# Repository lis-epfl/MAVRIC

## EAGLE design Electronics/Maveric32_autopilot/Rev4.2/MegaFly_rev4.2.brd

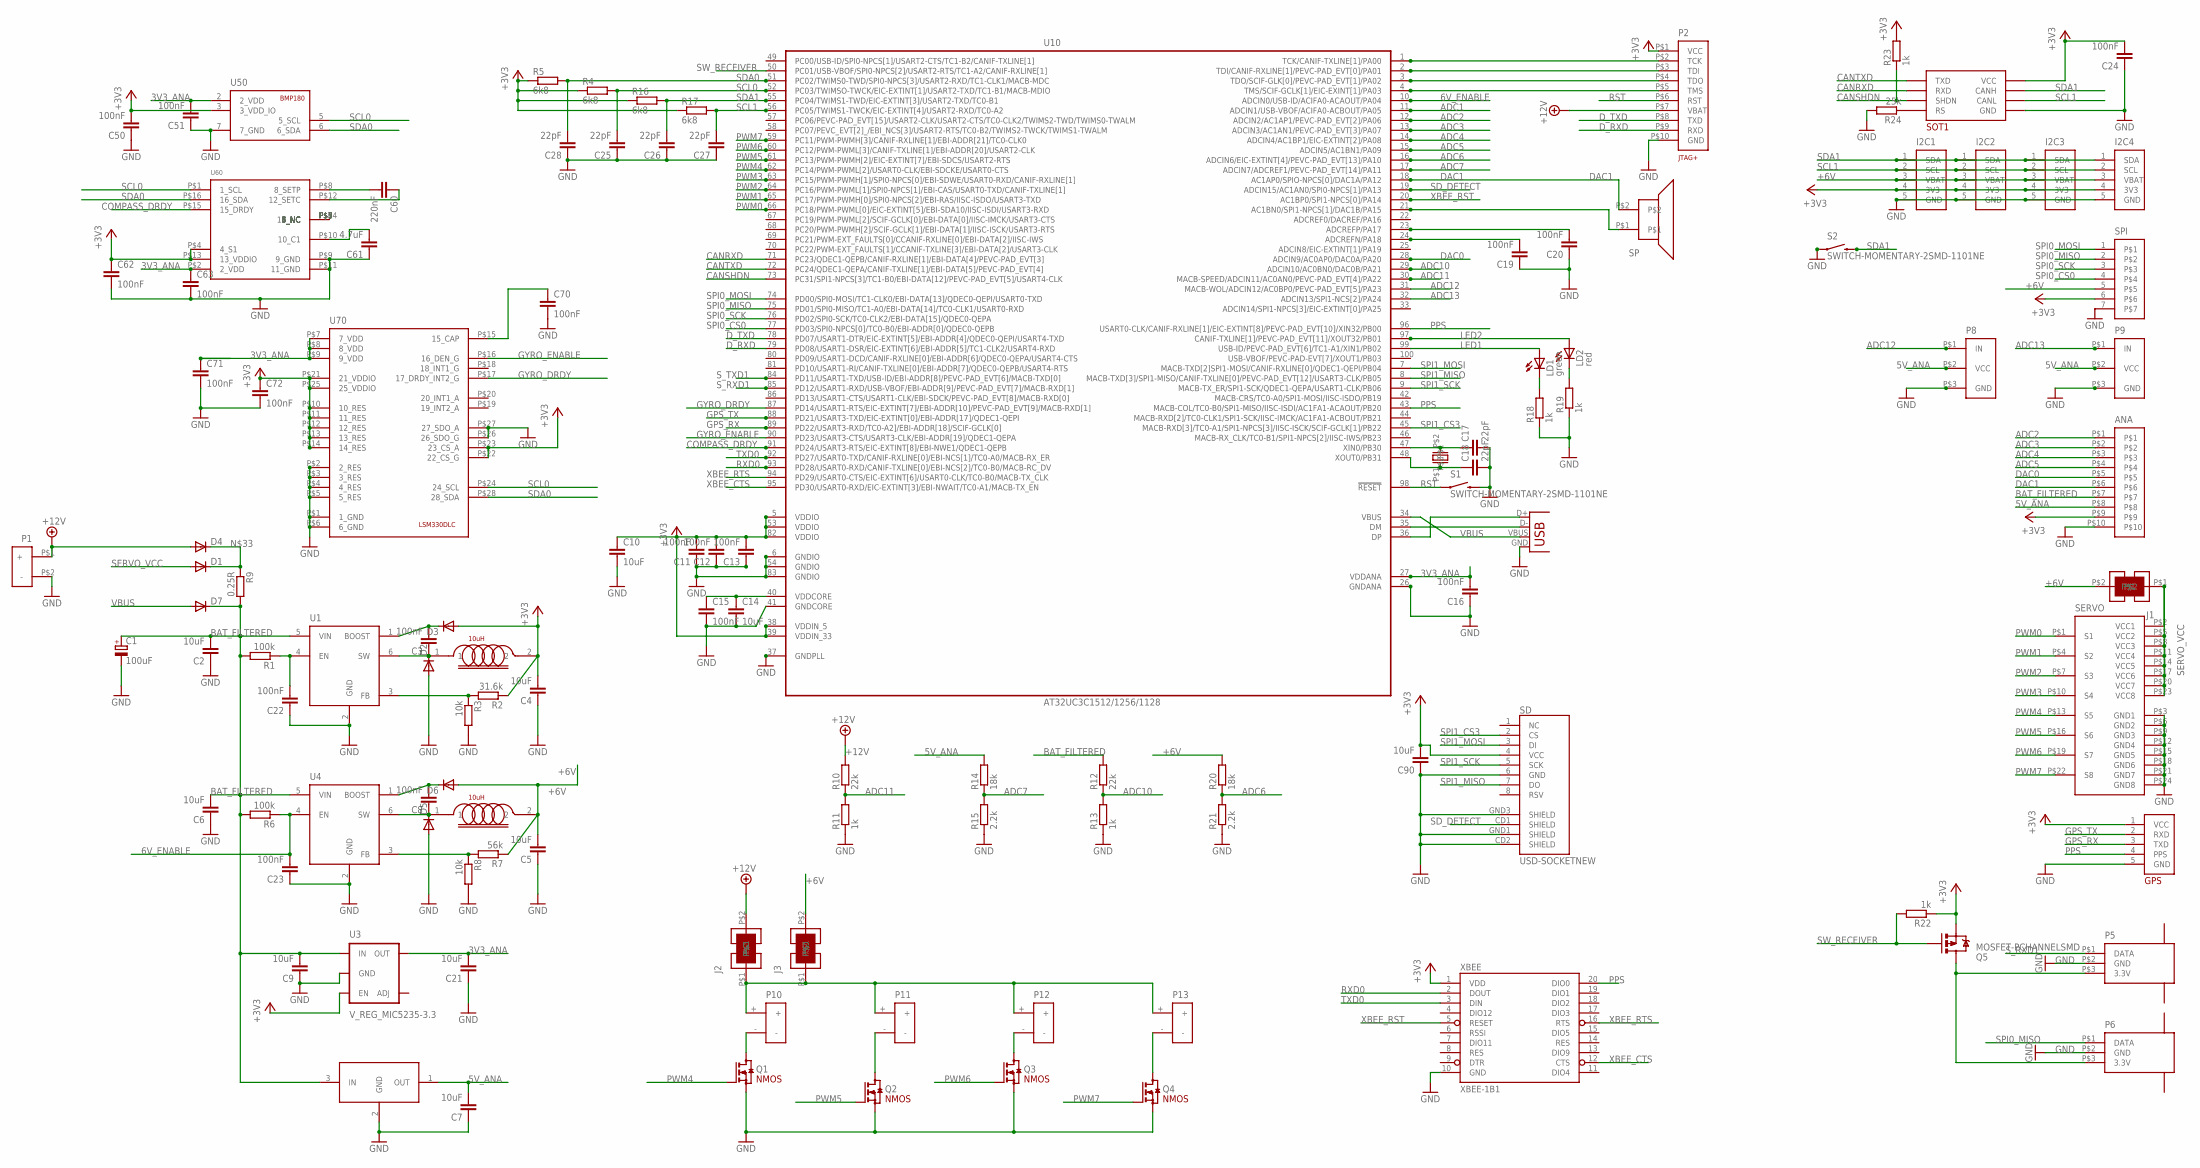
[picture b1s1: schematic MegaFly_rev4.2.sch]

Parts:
ANA: MOLEX_CONNECTOR_10PINSMOLEX_PICOBLADE; MOLEX_CONNECTOR_10PINS
C1: 100uF; D/7343-31R
C2, C4, C5, C6, C7, C9, C10, C14, C21, C90: 10uF; C0805
C3, C8, C11, C12, C13, C15, C16, C19, C20, C22, C23, C24, C50, C51, C62, C63, C70, C71, C72: 100nF; C0603
C17, C18, C25, C26, C27, C28: 22pF; C0402
C60: 220nF; C0805
C61: 4.7uF; C0805
D1, D2, D3, D4, D5, D6, D7: DIODESOD; SOD-323
GPS: APM2.5_GPS_HEADERVERTICAL; MOLEX_CONNECTOR_5_PINS_VERTICAL
I2C1, I2C2, I2C3, I2C4: I2C_BUS_PICOVERTICAL; MOLEX_CONNECTOR_5_PINS_VERTICAL
J1, J2, J3: SOLDER_JUMPER_2WAY
L1, L2: 10uH; C1210
LD1: green; CHIPLED_0805
LD2: red; CHIPLED_0805
P1: POWER
P2: AVR32_JTAG+SERIALMOLEX_PICOBLADE; MOLEX_CONNECTOR_10PINS
P5, P6: SPEKTRUM_RECEIVER; JST_1.5MM_3WAY
P8, P9: SENSOR; SERVO_COMPACT
P10, P11, P12, P13: POWERSMALL_SMD; POWER_SMALL_SMD
Q1, Q2, Q3, Q4: N-CHANNEL_SOT23; SOT23
Q5: MOSFET-PCHANNELSMD; SOT23-3
R1, R6: 100k; R0603
R2: 31.6k; R0603
R3, R8: 10k; R0603
R4, R5, R16, R17: 6k8; R0603
R7: 56k; R0603
R9: 0.25R; R0805
R10, R12: 22k; R0603
R11, R13, R18, R19, R22, R23: 1k; R0603
R14, R20: 18k; R0603
R15, R21: 2.2k; R0603
R24: 25k; R0603
S1, S2: SWITCH-MOMENTARY-2SMD-1101NE; TACTILE-SWITCH-1101NE
SD: USD-SOCKETNEW; MICRO-SD-SOCKET-PP
SERVO: SERVOCONNECTOR_X8STANDARD; HEADER3X8
SOT1: MAX3051; SOT23-8L
SP: PIEZO_SPEAKERSMALLER; PIEZO_CMT_1203-SMT-REDUCED_FOOTPRINT
SPI: MOLEX_CONNECTOR_7PINS
U1, U4: LM2734; SOT23-6
U2: MC78L05; SOT89
U3: V_REG_MIC5235-3.3; SOT23-5
U10: AT32UC3C1512/1256/1128; TQFP100
U50: BMP180
U60: HMC5883L; LPCC16_0.5MM
U70: LSM330DLC
USB: USB-MICROB
X1: CRYSTAL:ABM_16MHz; SMD_CRYSTAL_ABM
XBEE: XBEE-1B1; XBEE-1

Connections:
3V3_ANA: C16.2, C21.2, C51.2, C63.1, C71.1, U3.5 (OUT), U10.27 (VDDANA), U50.2 (2_VDD), U60.P$2 (2_VDD), U70.P$7 (7_VDD), U70.P$8 (8_VDD), U70.P$9 (9_VDD)
5V_ANA: ANA.P$8, C7.2, P8.P$2 (VCC), P9.P$2 (VCC), R14.2, U2.1 (OUT)
6V_ENABLE: C23.2, R6.1, U4.4 (EN), U10.10 (ADCIN0/USB-ID/ACIFA0-ACAOUT/PA04)
+3V3: ANA.P$9, C4.2, C10.1, C11.2, C12.2, C13.2, C24.2, C50.2, C62.1, C72.1, C90.2, D3.2 (A), GPS.1 (VCC), I2C1.4 (3V3), I2C2.4 (3V3), I2C3.4 (3V3), I2C4.4 (3V3), L1.2, P2.P$1 (VCC), Q5.2 (S), R2.1, R4.1, R5.1, R16.1, R17.1, R22.1, R23.2, SD.4 (VCC), SOT1.P$3 (VCC), SPI.6, U3.3 (EN), U10.5 (VDDIO), U10.38 (VDDIN_5), U10.39 (VDDIN_33), U10.53 (VDDIO), U10.82 (VDDIO), U50.3 (3_VDD_IO), U60.P$4 (4_S1), U60.P$13 (13_VDDIO), U70.P$10 (10_RES), U70.P$11 (11_RES), U70.P$12 (12_RES), U70.P$13 (13_RES), U70.P$14 (14_RES), U70.P$21 (21_VDDIO), U70.P$22 (22_CS_G), U70.P$23 (23_CS_A), U70.P$25 (25_VDDIO), XBEE.1 (VDD)
+6V: C5.2, D6.2 (A), I2C1.3 (VBAT), I2C2.3 (VBAT), I2C3.3 (VBAT), I2C4.3 (VBAT), J1.P$2, J3.P$2, L2.2, R7.1, R20.2, SPI.5
+12V: D4.2 (A), J2.P$2, P1.P$1 (+), P2.P$7 (VBAT), R10.2
ADC1: U10.11 (ADCIN1/USB-VBOF/ACIFA0-ACBOUT/PA05)
ADC2: ANA.P$1, U10.12 (ADCIN2/AC1AP1/PEVC-PAD_EVT[2]/PA06)
ADC3: ANA.P$2, U10.13 (ADCIN3/AC1AN1/PEVC-PAD_EVT[3]/PA07)
ADC4: ANA.P$3, U10.14 (ADCIN4/AC1BP1/EIC-EXTINT[2]/PA08)
ADC5: ANA.P$4, U10.15 (ADCIN5/AC1BN1/PA09)
ADC6: R20.1, R21.2, U10.16 (ADCIN6/EIC-EXTINT[4]/PEVC-PAD_EVT[13]/P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)
ADC7: R14.1, R15.2, U10.17 (ADCIN7/ADCREF1/PEVC-PAD_EVT[14]/PA11)
ADC10: R12.1, R13.2, U10.29 (ADCIN10/AC0BN0/DAC0B/PA21)
ADC11: R10.1, R11.2, U10.30 (MACB-SPEED/ADCIN11/AC0AN0/PEVC-PAD_EVT[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)
ADC12: P8.P$1 (IN), U10.31 (MACB-WOL/ADCIN12/AC0BP0/PEVC-PAD_EVT[5]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)
ADC13: P9.P$1 (IN), U10.32 (ADCIN13/SPI1-NCS[2]/PA24)
BAT_FILTERED: ANA.P$7, C1.+, C2.2, C6.2, C9.2, D7.1 (C), R1.2, R6.2, R9.2, R12.2, U1.5 (VIN), U2.3 (IN), U3.1 (IN), U4.5 (VIN)
CANRXD: SOT1.P$4 (RXD), U10.71 (PC23/QDEC1-QEPB/CANIF-RXLINE[1]/EBI-DAT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)
CANSHDN: R23.1, SOT1.P$5 (SHDN), U10.73 (PC31/SPI1-NPCS[3]/TC1-B0/EBI-DATA[12]/P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)
CANTXD: SOT1.P$1 (TXD), U10.72 (PC24/QDEC1-QEPA/CANIF-TXLINE[1]/EBI-DAT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)
COMPASS_DRDY: U10.91 (PD24/USART3-RTS/EIC-EXTINT[8]/EBI-NWE1/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), U60.P$15 (15_DRDY)
DAC0: ANA.P$5, U10.28 (ADCIN9/AC0AP0/DAC0A/PA20)
DAC1: ANA.P$6, SP.P$2, U10.18 (AC1AP0/SPIO-NPCS[0]/DAC1A/PA12)
D_RXD: P2.P$9 (RXD), U10.79 (PD08/USART1-DSR/EIC-EXTINT[6]/EBI-ADDR[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)
D_TXD: P2.P$8 (TXD), U10.78 (PD07/USART1-DTR/EIC-EXTINT[5]/EBI-ADDR[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)
GND: ANA.P$10, C1.-, C2.1, C4.1, C5.1, C6.1, C7.1, C9.1, C10.2, C11.1, C12.1, C13.1, C14.2, C15.2, C16.1, C17.2, C18.2, C19.1, C20.1, C21.1, C22.1, C23.1, C24.1, C25.1, C26.1, C27.1, C28.1, C50.1, C51.1, C61.1, C62.2, C63.2, C70.2, C71.2, C72.2, C90.1, D2.2 (A), D5.2 (A), GPS.5 (GND), I2C1.5 (GND), I2C2.5 (GND), I2C3.5 (GND), I2C4.5 (GND), P1.P$2 (-), P2.P$10 (GND), P5.P$2 (GND), P6.P$2 (GND), P8.P$3 (GND), P9.P$3 (GND), Q1.2 (S), Q2.2 (S), Q3.2 (S), Q4.2 (S), R3.2, R8.2, R11.1, R13.1, R15.1, R18.1, R19.1, R21.1, R24.2, S1.P$2 (2), S2.P$1 (1), SD.6 (GND), SD.CD2 (SHIELD), SD.GND1 (SHIELD), SD.GND3 (SHIELD), SERVO.P$3 (GND1), SERVO.P$6 (GND2), SERVO.P$9 (GND3), SERVO.P$12 (GND4), SERVO.P$15 (GND5), SERVO.P$18 (GND6), SERVO.P$21 (GND7), SERVO.P$24 (GND8), SOT1.P$2 (GND), SPI.7, U1.2 (GND), U2.2 (GND), U3.2 (GND), U4.2 (GND), U10.6 (GNDIO), U10.26 (GNDANA), U10.37 (GNDPLL), U10.41 (GNDCORE), U10.54 (GNDIO), U10.83 (GNDIO), U50.7 (7_GND), U60.P$9 (9_GND), U60.P$11 (11_GND), U70.P$1 (1_GND), U70.P$2 (2_RES), U70.P$3 (3_RES), U70.P$4 (4_RES), U70.P$5 (5_RES), U70.P$6 (6_GND), U70.P$26 (26_SDO_G), U70.P$27 (27_SDO_A), USB.GND, XBEE.10 (GND)
GPS_RX: GPS.3 (TXD), U10.89 (PD22/USART3-RXD/TC0-A2]/EBI-ADDR[18]/SC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)
GPS_TX: GPS.2 (RXD), U10.88 (PD21/USART3-TXD/EIC-EXTINT[0]/EBI-ADDR[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)
GYRO_DRDY: U10.87 (PD14/USART1-RTS/EIC-EXTINT[7]/EBI-ADDR[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), U70.P$17 (17_DRDY_INT2_G)
GYRO_ENABLE: U10.90 (PD23/USART3-CTS/USART3-CLK/EBI-ADDR[19]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), U70.P$16 (16_DEN_G)
LED1: LD1.A, U10.99 (USB-ID/PEVC-PAD_EVT[6]/TC1-A1/XIN1/PB02)
LED2: LD2.A, U10.97 (CANIF-TXLINE[1]/PEVC-PAD_EVT[11]/XOUT32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)
unnamed: P2.P$5 (TMS), U10.4 (TMS/SCIF-GCLK[1]/EIC-EXINT[1]/PA03)
unnamed: P2.P$4 (TDO), U10.3 (TDO/SCIF-GLK[0]/PEVC-PAD_EVT[1]/PA02)
unnamed: C18.1, U10.48 (XOUT0/PB31), X1.P$1
unnamed: C17.1, U10.47 (XIN0/PB30), X1.P$2
unnamed: LD1.C, R18.2
unnamed: C22.2, R1.1, U1.4 (EN)
unnamed: LD2.C, R19.2
unnamed: C3.1, D2.1 (C), L1.1, U1.6 (SW)
unnamed: R2.2, R3.1, U1.3 (FB)
unnamed: C3.2, D3.1 (C), U1.1 (BOOST)
unnamed: SP.P$1, U10.21 (AC1BN0/SPI1-NPCS[1]/DAC1B/PA15)
unnamed: C61.2, U60.P$10 (10_C1)
unnamed: C60.2, U60.P$8 (8_SETP)
unnamed: C60.1, U60.P$12 (12_SETC)
unnamed: C70.1, U70.P$15 (15_CAP)
unnamed: J2.P$1, J3.P$1, P10.+, P11.+, P12.+, P13.+
unnamed: P2.P$3 (TDI), U10.2 (TDI/CANIF-RXLINE[1]/PEVC-PAD_EVT[0]/PA01)
unnamed: C8.1, D5.1 (C), L2.1, U4.6 (SW)
unnamed: C14.1, C15.1, U10.40 (VDDCORE)
unnamed: R7.2, R8.1, U4.3 (FB)
unnamed: C8.2, D6.1 (C), U4.1 (BOOST)
unnamed: P10.-, Q1.3 (D)
unnamed: P11.-, Q2.3 (D)
unnamed: P12.-, Q3.3 (D)
unnamed: P13.-, Q4.3 (D)
unnamed: U10.36 (DP), USB.D+
unnamed: P2.P$2 (TCK), U10.1 (TCK/CANIF-TXLINE[1]/PA00)
unnamed: U10.35 (DM), USB.D-
unnamed: C19.2, U10.24 (ADCREFN/PA18)
unnamed: C20.2, U10.23 (ADCREFP/PA17)
unnamed: D1.1 (C), D4.1 (C), R9.1
unnamed: P5.P$3 (3.3V), P6.P$3 (3.3V), Q5.3 (D)
unnamed: R24.1, SOT1.P$8 (RS)
PPS: GPS.4 (PPS), U10.43 (MACB-COL/TC0-B0/SPI1-MISO/IISC-ISDI/AC1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), U10.96 (USART0-CLK/CANIF-RXLINE[1]/EIC-EXTINT[8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), XBEE.20 (DIO0)
PWM0: SERVO.P$1 (S1), U10.66 (PC18/PWM-PWML[0]/EIC-EXTINT[5]/EBI-SDA1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)
PWM1: SERVO.P$4 (S2), U10.65 (PC17/PWM-PWMH[0]/SPI0-NPCS[2]/EBI-RAS/I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)
PWM2: SERVO.P$7 (S3), U10.64 (PC16/PWM-PWML[1]/SPI0-NPCS[1]/EBI-CAS/U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)
PWM3: SERVO.P$10 (S4), U10.63 (PC15/PWM-PWMH[1]/SPI0-NPCS[0]/EBI-SDWE/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)
PWM4: Q1.1 (G), SERVO.P$13 (S5), U10.62 (PC14/PWM-PWML[2]/USART0-CLK/EBI-SDCKE/U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)
PWM5: Q2.1 (G), SERVO.P$16 (S6), U10.61 (PC13/PWM-PWMH[2]/EIC-EXTINT[7]/EBI-SDCS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)
PWM6: Q3.1 (G), SERVO.P$19 (S7), U10.60 (PC12/PWM-PWML[3]/CANIF-TXLINE[1]/EBI-AD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)
PWM7: Q4.1 (G), SERVO.P$22 (S8), U10.59 (PC11/PWM-PWMH[3]/CANIF-RXLINE[1]/EBI-AD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)
RST: P2.P$6 (RST), S1.P$1 (1), U10.98 (!RESET)
RXD0: U10.93 (PD28/USART0-RXD/CANIF-TXLINE[0]/EBI-NCS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), XBEE.2 (DOUT)
SCL0: C25.2, R4.2, U10.52 (PC03/TWIMSO-TWCK/EIC-EXTINT[1]/USART2-T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), U50.5 (5_SCL), U60.P$1 (1_SCL), U70.P$24 (24_SCL)
SCL1: C27.2, I2C1.2 (SCL), I2C2.2 (SCL), I2C3.2 (SCL), I2C4.2 (SCL), R17.2, SOT1.P$6 (CANL), U10.56 (PC05/TWIMS1-TWCK/EIC-EXTINT[4]/USART2-R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)
SDA0: C28.2, R5.2, U10.51 (PC02/TWIMS0-TWD/SPI0-NPCS[3]/USART2-RXD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), U50.6 (6_SDA), U60.P$16 (16_SDA), U70.P$28 (28_SDA)
SDA1: C26.2, I2C1.1 (SDA), I2C2.1 (SDA), I2C3.1 (SDA), I2C4.1 (SDA), R16.2, S2.P$2 (2), SOT1.P$7 (CANH), U10.55 (PC04/TWIMS1-TWD/EIC-EXTINT[3]/USART2-TX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)
SD_DETECT: SD.CD1 (SHIELD), U10.19 (ADCIN15/AC1AN0/SPI0-NPCS[1]/PA13)
SERVO_VCC: D1.2 (A), J1.P$1, SERVO.P$2 (VCC1), SERVO.P$5 (VCC2), SERVO.P$8 (VCC3), SERVO.P$11 (VCC4), SERVO.P$14 (VCC5), SERVO.P$17 (VCC6), SERVO.P$20 (VCC7), SERVO.P$23 (VCC8)
SPI0_CS0: SPI.4, U10.77 (PD03/SPI0-NPCS[0]/TC0-B0/EBI-ADDR[0]/QD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)
SPI0_MISO: P6.P$1 (DATA), SPI.2, U10.75 (PD01/SPI0-MISO/TC1-A0/EBI-DATA[14]/TC0-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)
SPI0_MOSI: SPI.1, U10.74 (PD00/SPI0-MOSI/TC1-CLK0/EBI-DATA[13]/QD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)
SPI0_SCK: SPI.3, U10.76 (PD02/SPI0-SCK/TC0-CLK2/EBI-DATA[15]/QDE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)
SPI1_CS3: SD.2 (CS), U10.45 (MACB-RXD[3]/TC0-A1/SPI1-NPCS[3]/IISC-IS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)
SPI1_MISO: SD.7 (DO), U10.8 (MACB-TXD[3]/SPI1-MISO/CANIF-TXLINE[0]/P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)
SPI1_MOSI: SD.3 (DI), U10.7 (MACB-TXD[2]SPI1-MOSI/CANIF-RXLINE[0]/QD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)
SPI1_SCK: SD.5 (SCK), U10.9 (MACB-TX_ER/SPI1-SCK/QDEC1-QEPA/USART1-C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)
SW_RECEIVER: Q5.1 (G), R22.2, U10.50 (PC01/USB-VBOF/SPI0-NPCS[2]/USART2-RTS/T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)
S_RXD1: P5.P$1 (DATA), U10.85 (PD12/USART1-RXD/USB-VBOF/EBI-ADDR[9]/PE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)
S_TXD1: U10.84 (PD11/USART1-TXD/USB-ID/EBI-ADDR[8]/PEVC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)
TXD0: U10.92 (PD27/USART0-TXD/CANIF-RXLINE[0]/EBI-NCS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), XBEE.3 (DIN)
VBUS: D7.2 (A), U10.34 (VBUS), USB.VBUS
XBEE_CTS: U10.95 (PD30/USART0-RXD/EIC-EXTINT[3]/EBI-NWAIT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), XBEE.12 (CTS)
XBEE_RST: U10.20 (AC1BP0/SPI1-NPCS[0]/PA14), XBEE.5 (RESET)
XBEE_RTS: U10.94 (PD29/USART0-CTS/EIC-EXTINT[6]/USART0-CL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), XBEE.16 (RTS)

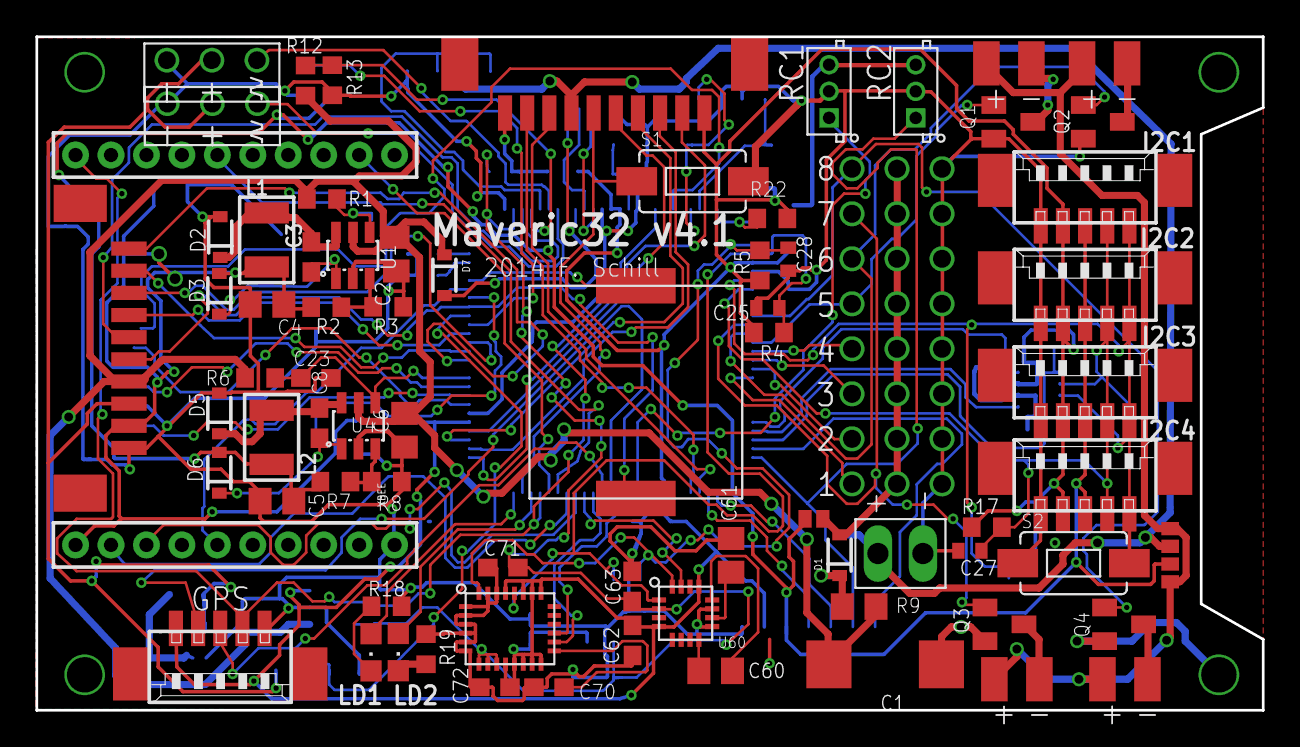
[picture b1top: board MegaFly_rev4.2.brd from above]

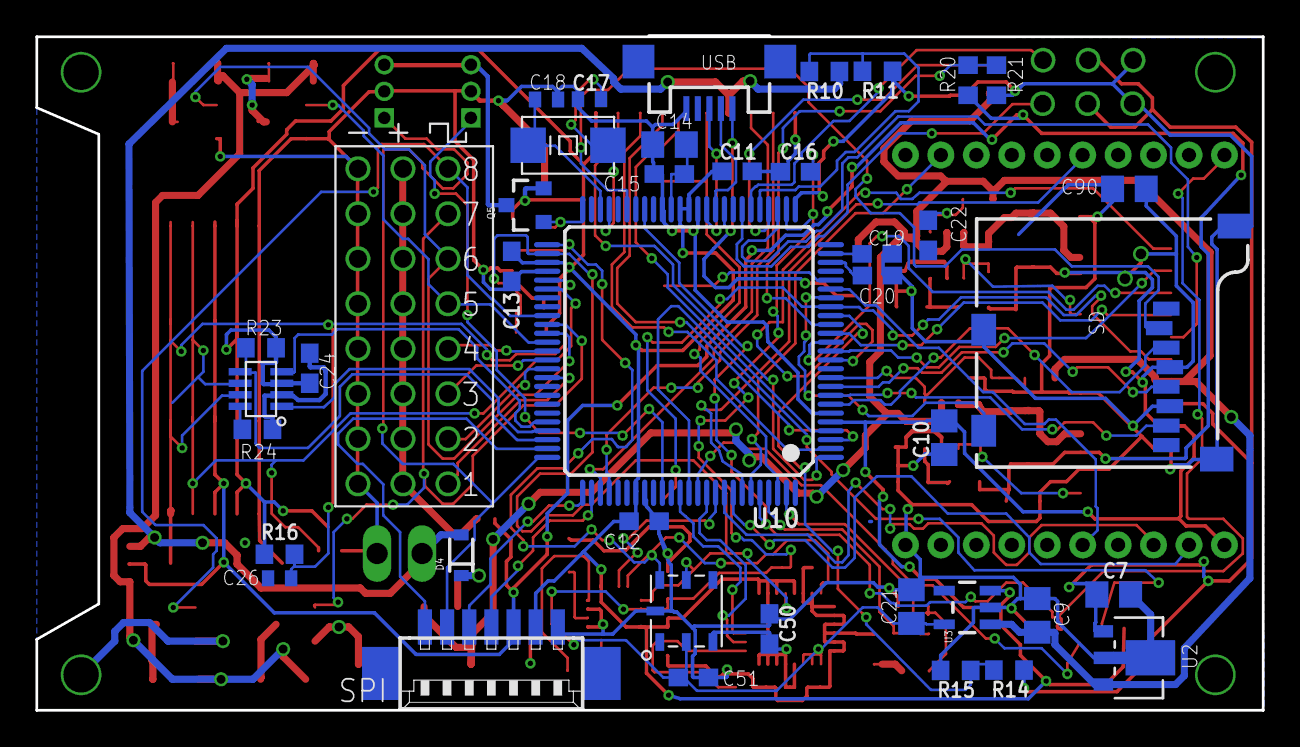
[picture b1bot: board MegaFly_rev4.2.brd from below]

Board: 2 copper layers, 69.2 x 38.0 mm, 115 parts (41 on the bottom side), 97 nets.

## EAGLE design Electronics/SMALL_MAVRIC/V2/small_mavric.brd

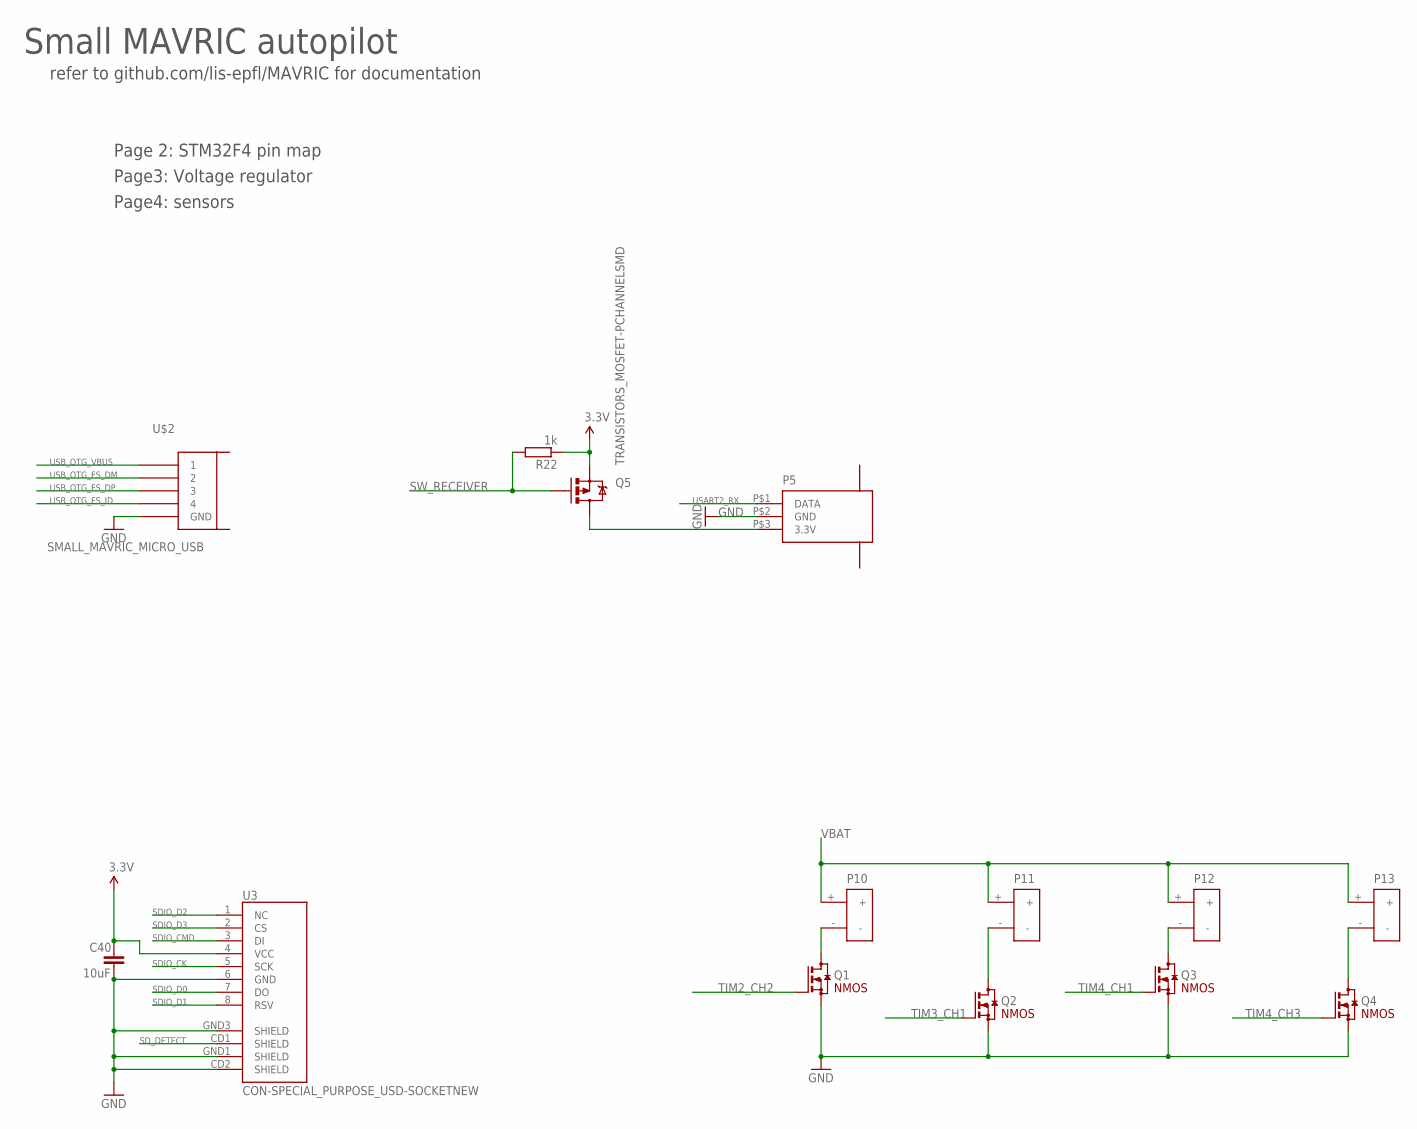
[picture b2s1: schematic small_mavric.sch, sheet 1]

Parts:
C40: 10uF; SMALL_MAVRIC_SMALL_MAVRIC_CAPACITOR_C0603; PARTNO 2.2UF 16V 0603
P5: CON-SPECIAL_PURPOSE_SPEKTRUM_RECEIVER; CON-SPECIAL_PURPOSE_JST_1.5MM_3WAY
P10, P11, P12, P13: POWERSMALL_SMD; POWER_SMALL_SMD
Q1, Q2, Q3, Q4: N-CHANNEL_SOT23; SOT23
Q5: TRANSISTORS_MOSFET-PCHANNELSMD; TRANSISTORS_SOT23-3
R22: 1k; SMALL_MAVRIC_SMALL_MAVRIC_RESISTOR_R0402
U3: CON-SPECIAL_PURPOSE_USD-SOCKETNEW; CON-SPECIAL_PURPOSE_MICRO-SD-SOCKET-PP
U$2: SMALL_MAVRIC_MICRO_USB; SMALL_MAVRIC_MICR0_USB

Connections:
3.3V: C40.1, Q5.2 (S), R22.1, U3.4 (VCC); also elsewhere on the board
GND: C40.2, P5.P$2 (GND), Q1.2 (S), Q2.2 (S), Q3.2 (S), Q4.2 (S), U3.6 (GND), U3.CD2 (SHIELD), U3.GND1 (SHIELD), U3.GND3 (SHIELD), U$2.5 (GND); also elsewhere on the board
unnamed: P11.-, Q2.3 (D)
unnamed: P12.-, Q3.3 (D)
unnamed: P10.-, Q1.3 (D)
unnamed: P13.-, Q4.3 (D)
unnamed: P5.P$3 (3.3V), Q5.3 (D)
SDIO_CK: U3.5 (SCK); also elsewhere on the board
SDIO_CMD: U3.3 (DI); also elsewhere on the board
SDIO_D0: U3.7 (DO); also elsewhere on the board
SDIO_D1: U3.8 (RSV); also elsewhere on the board
SDIO_D2: U3.1 (NC); also elsewhere on the board
SDIO_D3: U3.2 (CS); also elsewhere on the board
SD_DETECT: U3.CD1 (SHIELD); also elsewhere on the board
SW_RECEIVER: Q5.1 (G), R22.2; also elsewhere on the board
TIM2_CH2: Q1.1 (G); also elsewhere on the board
TIM3_CH1: Q2.1 (G); also elsewhere on the board
TIM4_CH1: Q3.1 (G); also elsewhere on the board
TIM4_CH3: Q4.1 (G); also elsewhere on the board
USART2_RX: P5.P$1 (DATA); also elsewhere on the board
USB_OTG_FS_DM: U$2.2; also elsewhere on the board
USB_OTG_FS_DP: U$2.3; also elsewhere on the board
USB_OTG_FS_ID: U$2.4; also elsewhere on the board
USB_OTG_VBUS: U$2.1; also elsewhere on the board
VBAT: P10.+, P11.+, P12.+, P13.+; also elsewhere on the board

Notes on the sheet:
Small MAVRIC autopilot
refer to github.com/lis-epfl/MAVRIC for documentation
Page 2: STM32F4 pin map
Page3: Voltage regulator
Page4: sensors

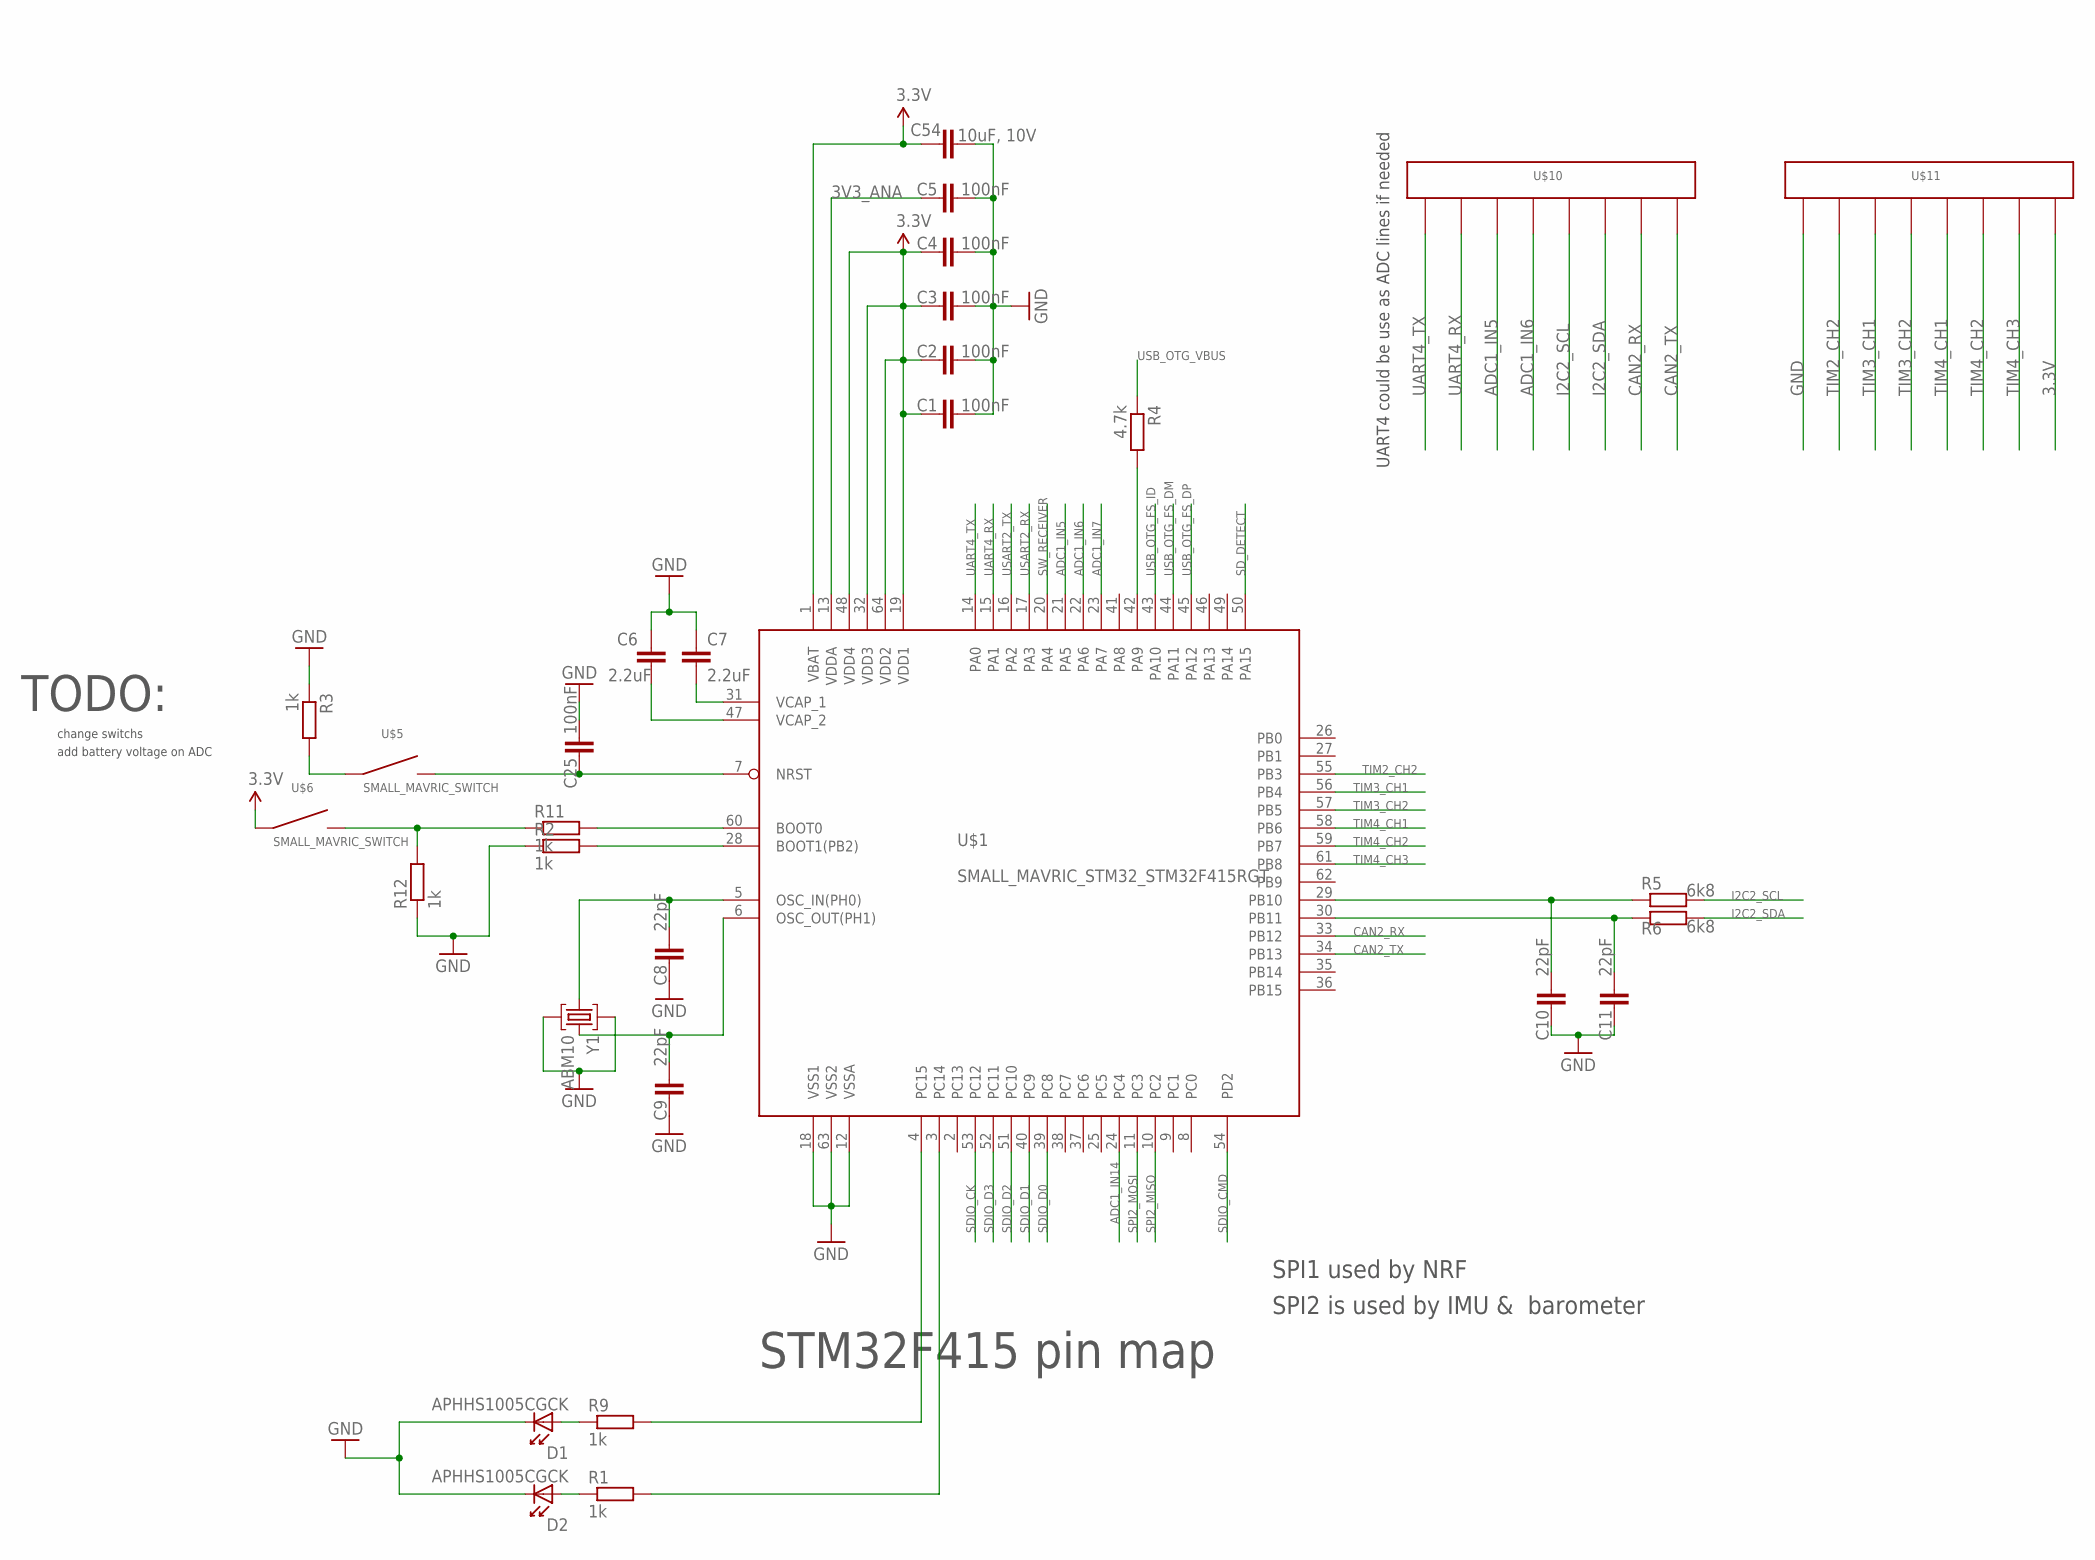
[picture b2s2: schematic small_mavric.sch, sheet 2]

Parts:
C1, C2, C3, C4, C5, C25: 100nF; SMALL_MAVRIC_SMALL_MAVRIC_CAPACITOR_C0402; PARTNO *
C6, C7: 2.2uF; SMALL_MAVRIC_SMALL_MAVRIC_CAPACITOR_C0603; PARTNO 2.2UF 16V 0603
C8, C9, C10, C11: 22pF; SMALL_MAVRIC_SMALL_MAVRIC_CAPACITOR_C0402; PARTNO *
C54: 10uF, 10V; SMALL_MAVRIC_SMALL_MAVRIC_CAPACITOR_C0603; PARTNO 10UF 10V 0805
D1, D2: APHHS1005CGCK; LED_0402; PARTNO APHHS1005CGCK
R1, R2, R3, R9, R11, R12: 1k; SMALL_MAVRIC_SMALL_MAVRIC_RESISTOR_R0402; PARTNO *
R4: 4.7k; SMALL_MAVRIC_SMALL_MAVRIC_RESISTOR_R0402; PARTNO *
R5, R6: 6k8; SMALL_MAVRIC_SMALL_MAVRIC_RESISTOR_R0402; PARTNO *
U$1: SMALL_MAVRIC_STM32_STM32F415RGT; SMALL_MAVRIC_STM32_LQFP64
U$5, U$6: SMALL_MAVRIC_SWITCH
U$10, U$11: SMALL_MAVRIC_CONN_RAIL_X8
Y1: ABM10; OSCILLATOR_ABM10; PARTNO ABM10 25MHz

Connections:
3.3V: C1.1, C2.1, C3.1, C4.1, C54.1, U$1.1 (VBAT), U$1.19 (VDD1), U$1.32 (VDD3), U$1.48 (VDD4), U$1.64 (VDD2), U$6.1, U$11.P$8; also elsewhere on the board
3V3_ANA: C5.1, U$1.13 (VDDA); also elsewhere on the board
ADC1_IN5: U$1.21 (PA5), U$10.P$3
ADC1_IN6: U$1.22 (PA6), U$10.P$4
ADC1_IN7: U$1.23 (PA7)
ADC1_IN14: U$1.24 (PC4)
CAN2_RX: U$1.33 (PB12), U$10.P$7
CAN2_TX: U$1.34 (PB13), U$10.P$8
GND: C1.2, C2.2, C3.2, C4.2, C5.2, C6.1, C7.1, C8.1, C9.1, C10.1, C11.1, C25.2, C54.2, D1.C, D2.C, R2.1, R3.1, R12.1, U$1.12 (VSSA), U$1.18 (VSS1), U$1.63 (VSS2), U$11.P$1, Y1.2, Y1.4; also elsewhere on the board
I2C2_SCL: R5.2, U$10.P$5; also elsewhere on the board
I2C2_SD: C11.2, R6.1, U$1.30 (PB11)
I2C2_SDA: R6.2, U$10.P$6; also elsewhere on the board
unnamed: D2.A, R1.1
unnamed: C8.2, U$1.5 (OSC_IN(PH0)), Y1.1
unnamed: R2.2, U$1.28 (BOOT1(PB2))
unnamed: C7.2, U$1.31 (VCAP_1)
unnamed: C6.2, U$1.47 (VCAP_2)
unnamed: C9.2, U$1.6 (OSC_OUT(PH1)), Y1.3
unnamed: R4.2, U$1.42 (PA9)
unnamed: R3.2, U$5.1
unnamed: D1.A, R9.1
unnamed: R1.2, U$1.3 (PC14)
unnamed: R9.2, U$1.4 (PC15)
unnamed: C25.1, U$1.7 (NRST), U$5.2
unnamed: R11.2, U$1.60 (BOOT0)
unnamed: C10.2, R5.1, U$1.29 (PB10)
unnamed: R11.1, R12.2, U$6.2
SDIO_CK: U$1.53 (PC12); also elsewhere on the board
SDIO_CMD: U$1.54 (PD2); also elsewhere on the board
SDIO_D0: U$1.39 (PC8); also elsewhere on the board
SDIO_D1: U$1.40 (PC9); also elsewhere on the board
SDIO_D2: U$1.51 (PC10); also elsewhere on the board
SDIO_D3: U$1.52 (PC11); also elsewhere on the board
SD_DETECT: U$1.50 (PA15); also elsewhere on the board
SPI2_MISO: U$1.10 (PC2)
SPI2_MOSI: U$1.11 (PC3)
SW_RECEIVER: U$1.20 (PA4); also elsewhere on the board
TIM2_CH2: U$1.55 (PB3), U$11.P$2; also elsewhere on the board
TIM3_CH1: U$1.56 (PB4), U$11.P$3; also elsewhere on the board
TIM3_CH2: U$1.57 (PB5), U$11.P$4
TIM4_CH1: U$1.58 (PB6), U$11.P$5; also elsewhere on the board
TIM4_CH2: U$1.59 (PB7), U$11.P$6
TIM4_CH3: U$1.61 (PB8), U$11.P$7; also elsewhere on the board
UART4_RX: U$1.15 (PA1), U$10.P$2
UART4_TX: U$1.14 (PA0), U$10.P$1
USART2_RX: U$1.17 (PA3); also elsewhere on the board
USART2_TX: U$1.16 (PA2)
USB_OTG_FS_DM: U$1.44 (PA11); also elsewhere on the board
USB_OTG_FS_DP: U$1.45 (PA12); also elsewhere on the board
USB_OTG_FS_ID: U$1.43 (PA10); also elsewhere on the board
USB_OTG_VBUS: R4.1; also elsewhere on the board

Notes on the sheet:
TODO:
change switchs
STM32F415 pin map
SPI2 is used by IMU & barometer
SPI1 used by NRF
add battery voltage on ADC
UART4 could be use as ADC lines if needed

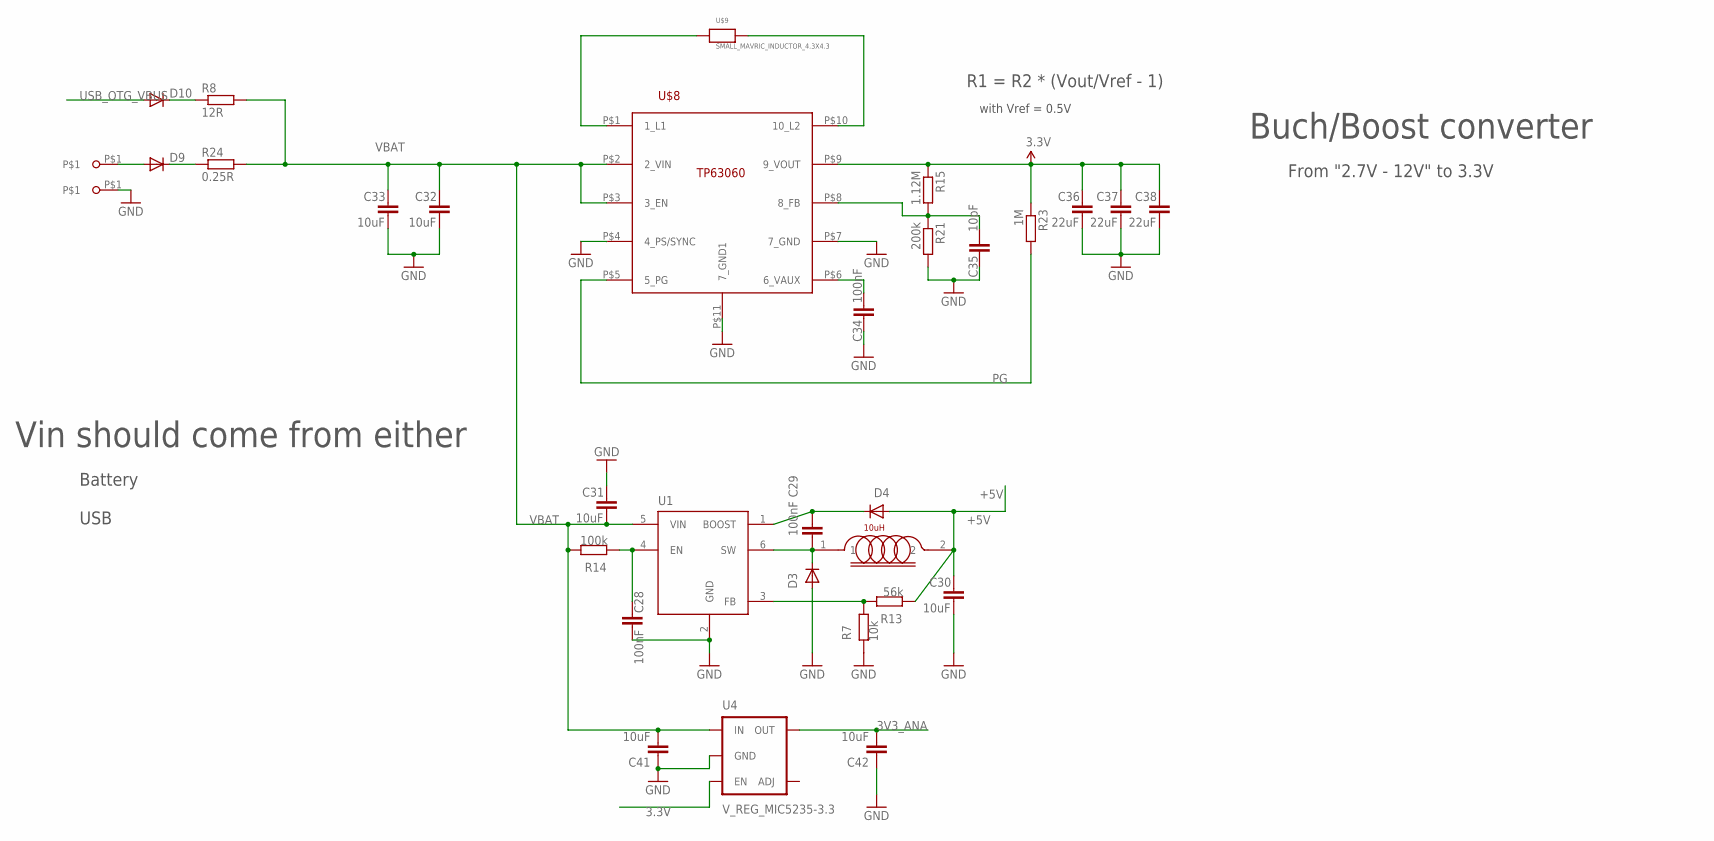
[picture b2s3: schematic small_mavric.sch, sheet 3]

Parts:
C28, C29, C34: 100nF; SMALL_MAVRIC_SMALL_MAVRIC_CAPACITOR_C0402; PARTNO *
C30, C31, C32, C33: 10uF; SMALL_MAVRIC_SMALL_MAVRIC_CAPACITOR_C0603; PARTNO 2.2UF 16V 0603
C35: 10pF; SMALL_MAVRIC_SMALL_MAVRIC_CAPACITOR_C0402; PARTNO *
C36, C37, C38: 22uF; SMALL_MAVRIC_SMALL_MAVRIC_CAPACITOR_C0603; PARTNO 2.2UF 16V 0603
C41, C42: 10uF; C0805
D3, D4, D9, D10: SMALL_MAVRIC_POWER_DIODESOD; SMALL_MAVRIC_POWER_SOD-323
L1: 10uH; POWER_C1210
R7: 10k; SMALL_MAVRIC_SMALL_MAVRIC_RESISTOR_R0402; PARTNO *
R8: 12R; SMALL_MAVRIC_SMALL_MAVRIC_RESISTOR_R0402; PARTNO *
R13: 56k; SMALL_MAVRIC_SMALL_MAVRIC_RESISTOR_R0402; PARTNO *
R14: 100k; SMALL_MAVRIC_SMALL_MAVRIC_RESISTOR_R0402; PARTNO *
R15: 1.12M; SMALL_MAVRIC_SMALL_MAVRIC_RESISTOR_R0402; PARTNO *
R21: 200k; SMALL_MAVRIC_SMALL_MAVRIC_RESISTOR_R0402; PARTNO *
R23: 1M; SMALL_MAVRIC_SMALL_MAVRIC_RESISTOR_R0402; PARTNO *
R24: 0.25R; SMALL_MAVRIC_SMALL_MAVRIC_RESISTOR_R0402; PARTNO *
U1: POWER_LM2734; POWER_SOT23-6
U4: V_REG_MIC5235-3.3; SOT23-5
U$8: SMALL_MAVRIC_POWER_TPS63060; SMALL_MAVRIC_POWER_PWSON
U$9: SMALL_MAVRIC_INDUCTOR_4.3X4.3; SMALL_MAVRIC_SMALL_MAVRIC_SMALL_MAVRIC_INDUCTOR_4.3X4.3
U$15, U$16: SMALL_MAVRIC_SMALL_CONNECTOR; SMALL_MAVRIC_SMALL_CONN

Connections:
3.3V: C36.1, C37.1, C38.1, R15.1, R23.1, U4.3 (EN), U$8.P$9 (9_VOUT); also elsewhere on the board
3V3_ANA: C42.2, U4.5 (OUT); also elsewhere on the board
6V_ENABLE1: C28.1, R14.1, U1.4 (EN)
+5V: C30.1, D4.2 (A), L1.2, R13.1
GND: C28.2, C30.2, C31.1, C32.2, C33.2, C34.1, C35.1, C36.2, C37.2, C38.2, C41.1, C42.1, D3.2 (A), R7.1, R21.2, U1.2 (GND), U4.2 (GND), U$8.P$4 (4_PS/SYNC), U$8.P$7 (7_GND), U$8.P$11 (7_GND1), U$15.P$1; also elsewhere on the board
unnamed: D10.1 (C), R8.1
unnamed: C29.2, D3.1 (C), L1.1, U1.6 (SW)
unnamed: R7.2, R13.2, U1.3 (FB)
unnamed: C29.1, D4.1 (C), U1.1 (BOOST)
unnamed: U$8.P$1 (1_L1), U$9.P$1
unnamed: U$8.P$10 (10_L2), U$9.P$2
unnamed: C34.2, U$8.P$6 (6_VAUX)
unnamed: C35.2, R15.2, R21.1, U$8.P$8 (8_FB)
unnamed: D9.2 (A), U$16.P$1
unnamed: D9.1 (C), R24.1
PG: R23.2, U$8.P$5 (5_PG)
USB_OTG_VBUS: D10.2 (A); also elsewhere on the board
VBAT: C31.2, C32.1, C33.1, C41.2, R8.2, R14.2, R24.2, U1.5 (VIN), U4.1 (IN), U$8.P$2 (2_VIN), U$8.P$3 (3_EN); also elsewhere on the board

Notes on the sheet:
Buch/Boost converter
From "2.7V - 12V" to 3.3V
R1 = R2 * (Vout/Vref - 1)
with Vref = 0.5V
Vin should come from either
Battery
USB

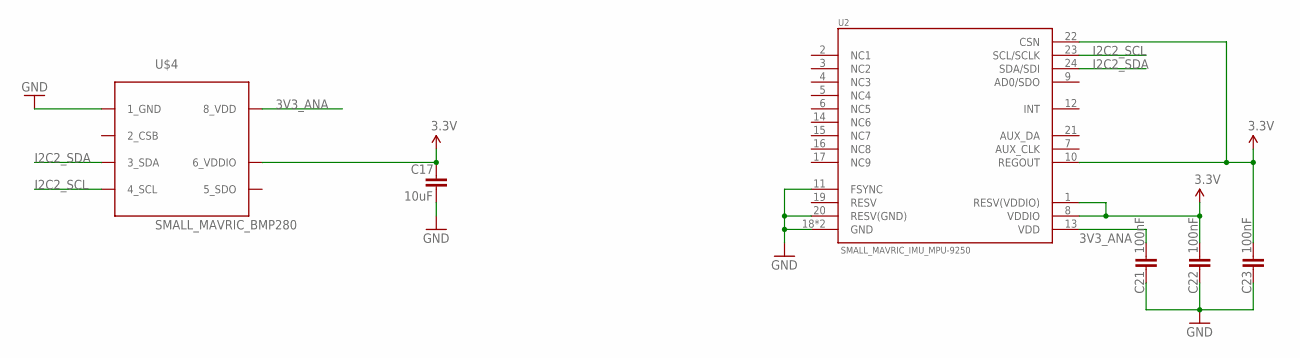
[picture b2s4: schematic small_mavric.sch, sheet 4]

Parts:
C17: 10uF; SMALL_MAVRIC_SMALL_MAVRIC_CAPACITOR_C0603; PARTNO 2.2UF 16V 0603
C21, C22, C23: 100nF; SMALL_MAVRIC_SMALL_MAVRIC_CAPACITOR_C0402; PARTNO *
U2: SMALL_MAVRIC_IMU_MPU-9250; SMALL_MAVRIC_SMALL_MAVRIC_QFN-24_3.0X3.0MM
U$4: SMALL_MAVRIC_BMP280; SMALL_MAVRIC_SMALL_MAVRIC_SMALL_MAVRIC_LGA-8

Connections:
3.3V: C17.1, C22.2, C23.2, U2.1 (RESV(VDDIO)), U2.8 (VDDIO), U2.10 (REGOUT), U2.22 (CSN), U$4.P$6 (6_VDDIO); also elsewhere on the board
3V3_ANA: C21.2, U2.13 (VDD), U$4.P$8 (8_VDD); also elsewhere on the board
GND: C17.2, C21.1, C22.1, C23.1, U2.11 (FSYNC), U2.18 (GND), U2.20 (RESV(GND)), U2.CENTRAL_PAD (GND), U$4.P$1 (1_GND), U$4.P$7 (1_GND); also elsewhere on the board
I2C2_SCL: U2.23 (SCL/SCLK), U$4.P$4 (4_SCL); also elsewhere on the board
I2C2_SDA: U2.24 (SDA/SDI), U$4.P$3 (3_SDA); also elsewhere on the board

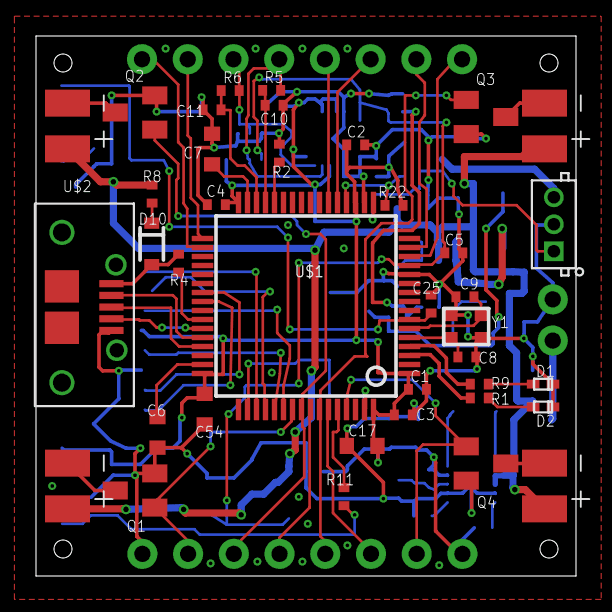
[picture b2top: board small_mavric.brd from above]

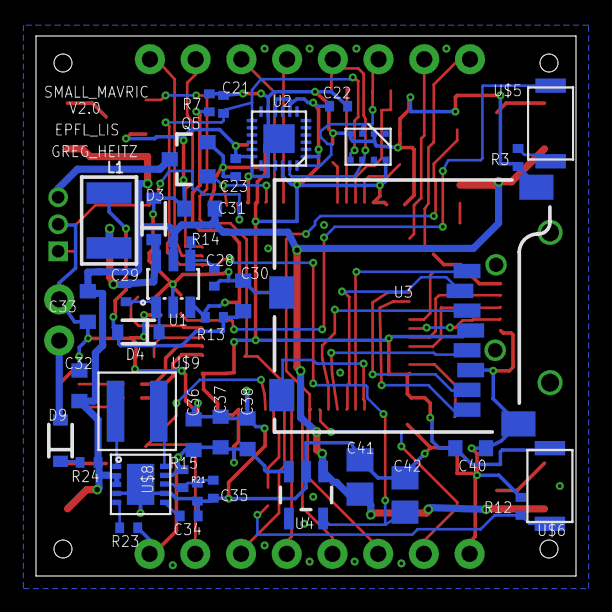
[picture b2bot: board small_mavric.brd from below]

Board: 2 copper layers, 30.0 x 30.0 mm, 82 parts (40 on the bottom side), 65 nets.

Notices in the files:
parts and their libraries:
SparkFun-DigitalIC: Licensing: Creative Commons ShareAlike 4.0 International - https://creativecommons.org/licenses/by-sa/4.0
